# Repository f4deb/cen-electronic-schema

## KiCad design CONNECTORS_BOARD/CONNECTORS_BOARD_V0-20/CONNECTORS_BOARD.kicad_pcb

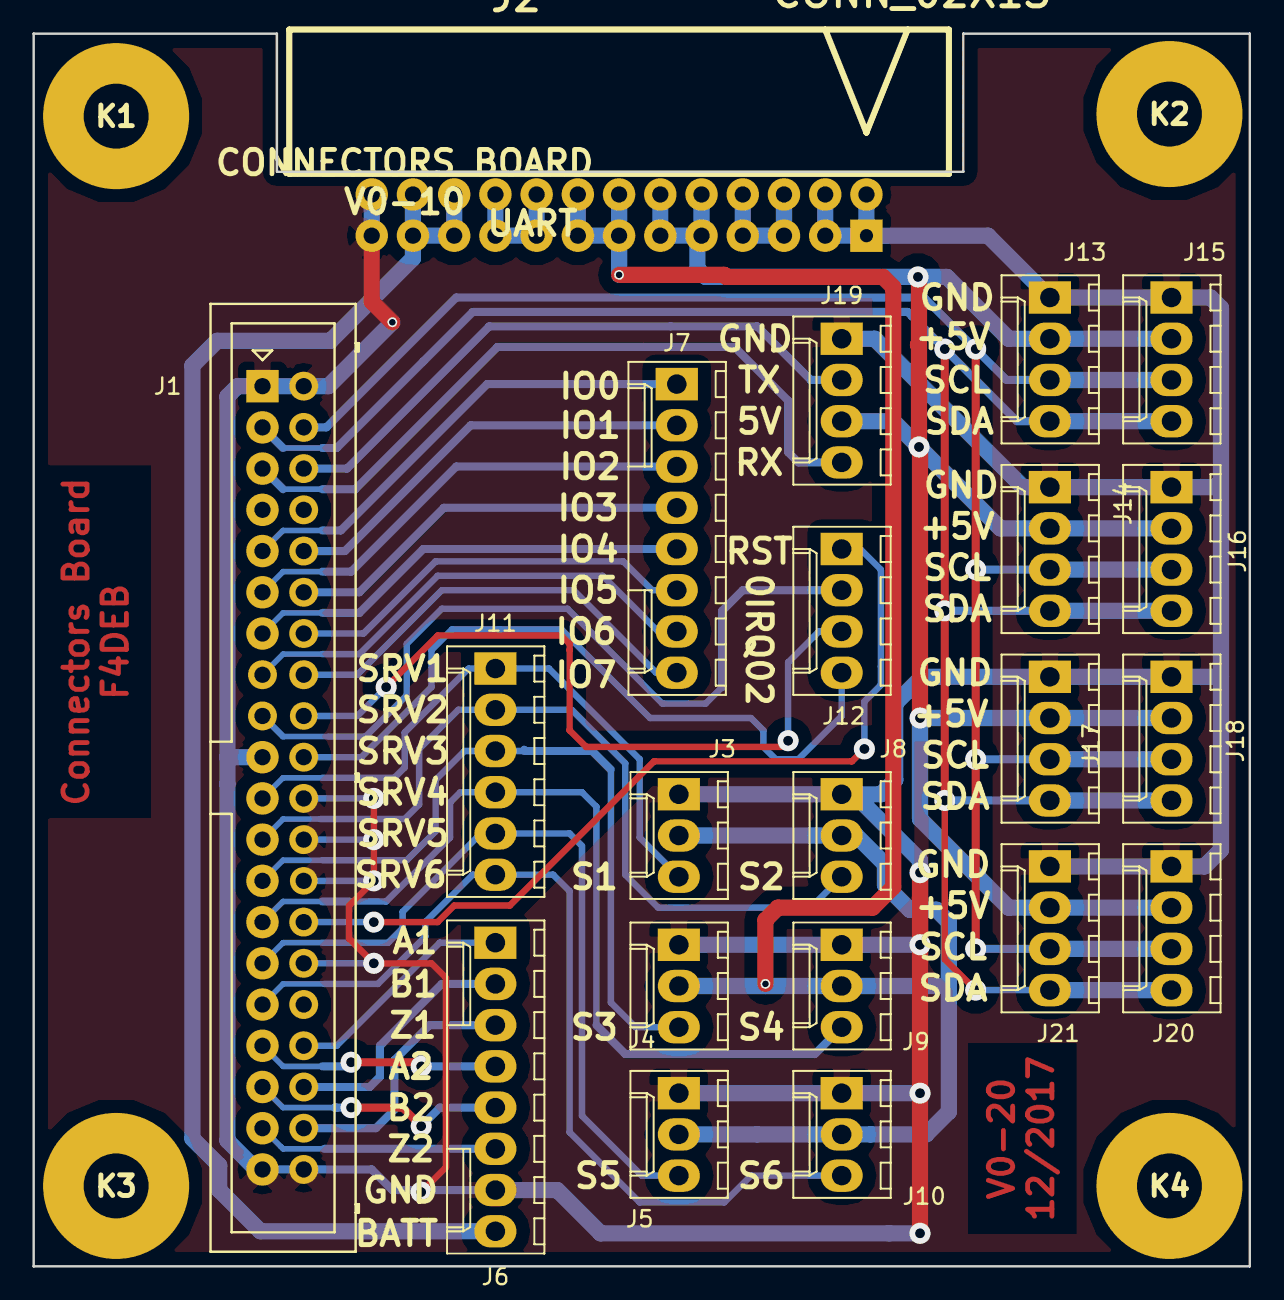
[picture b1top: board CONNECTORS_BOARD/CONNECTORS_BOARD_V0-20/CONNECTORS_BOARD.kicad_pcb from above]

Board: 2 copper layers, 74.9 x 75.9 mm, 25 parts (0 on the bottom side), 34 nets.

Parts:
J1: CONN_02X20; Multicomp_MC9A12-4034_2x20x2.54mm_Straight
J2: CONN_02X13; he10-26c-f
J3, J4, J5, J8, J9, J10: CONN_01X03; Molex_KK-6410-03_03x2.54mm_Straight
J6, J7: CONN_01X08; Molex_KK-6410-08_08x2.54mm_Straight
J11: CONN_01X06; Molex_KK-6410-06_06x2.54mm_Straight
J12, J13, J14, J15, J16, J17, J18, J19, J20, J21: CONN_01X04; Molex_KK-6410-04_04x2.54mm_Straight
K1, K2, K3, K4: COLONETTE

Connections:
+3V3: J2.5, J2.6, J2.7, J2.8
+5V: J2.9, J2.10, J2.11, J2.12, J13.2, J14.2, J15.2, J16.2, J17.2, J18.2, J19.3, J20.2, J21.2
+5VA: J2.13, J2.14, J2.15, J2.16, J3.2, J4.2, J5.2, J8.2, J9.2, J10.2
+12V: J2.17, J2.18, J2.19, J2.20
+BATT: J2.21, J2.22, J2.23, J2.24, J6.8
/A1: J1.34, J6.1
/A2: J1.33, J6.4
/B1: J1.36, J6.2
/B2: J1.35, J6.5
/IO0: J1.9, J7.1
/IO1: J1.10, J7.2
/IO2: J1.11, J7.3
/IO3: J1.12, J7.4
/IO4: J1.13, J7.5
/IO5: J1.14, J7.6
/IO6: J1.15, J7.7
/IO7: J1.16, J7.8
/IRQ0: J1.17, J12.2
/IRQ1: J1.18, J12.3
/IRQ2: J1.20, J12.4
/RST: J1.28, J12.1
/RX: J1.5, J19.4
/SCL: J1.4, J13.3, J14.3, J15.3, J16.3, J17.3, J18.3, J20.3, J21.3
/SDA: J1.3, J13.4, J14.4, J15.4, J16.4, J17.4, J18.4, J20.4, J21.4
/SERV1: J1.21, J3.3, J11.1
/SERV2: J1.23, J8.3, J11.2
/SERV3: J1.25, J4.3, J11.3
/SERV4: J1.27, J9.3, J11.4
/SERV5: J1.29, J5.3, J11.5
/SERV6: J1.31, J10.3, J11.6
/TX: J1.6, J19.2
/Z1: J1.38, J6.3
/Z2: J1.37, J6.6
GND: J1.1, J1.2, J1.19, J1.22, J1.24, J1.26, J1.30, J1.39, J1.40, J2.1, J2.2, J2.3, J2.4, J2.25, J2.26, J3.1, J4.1, J5.1, J6.7, J8.1, J9.1, J10.1, J13.1, J14.1, J15.1, J16.1, J17.1, J18.1, J19.1, J20.1, J21.1

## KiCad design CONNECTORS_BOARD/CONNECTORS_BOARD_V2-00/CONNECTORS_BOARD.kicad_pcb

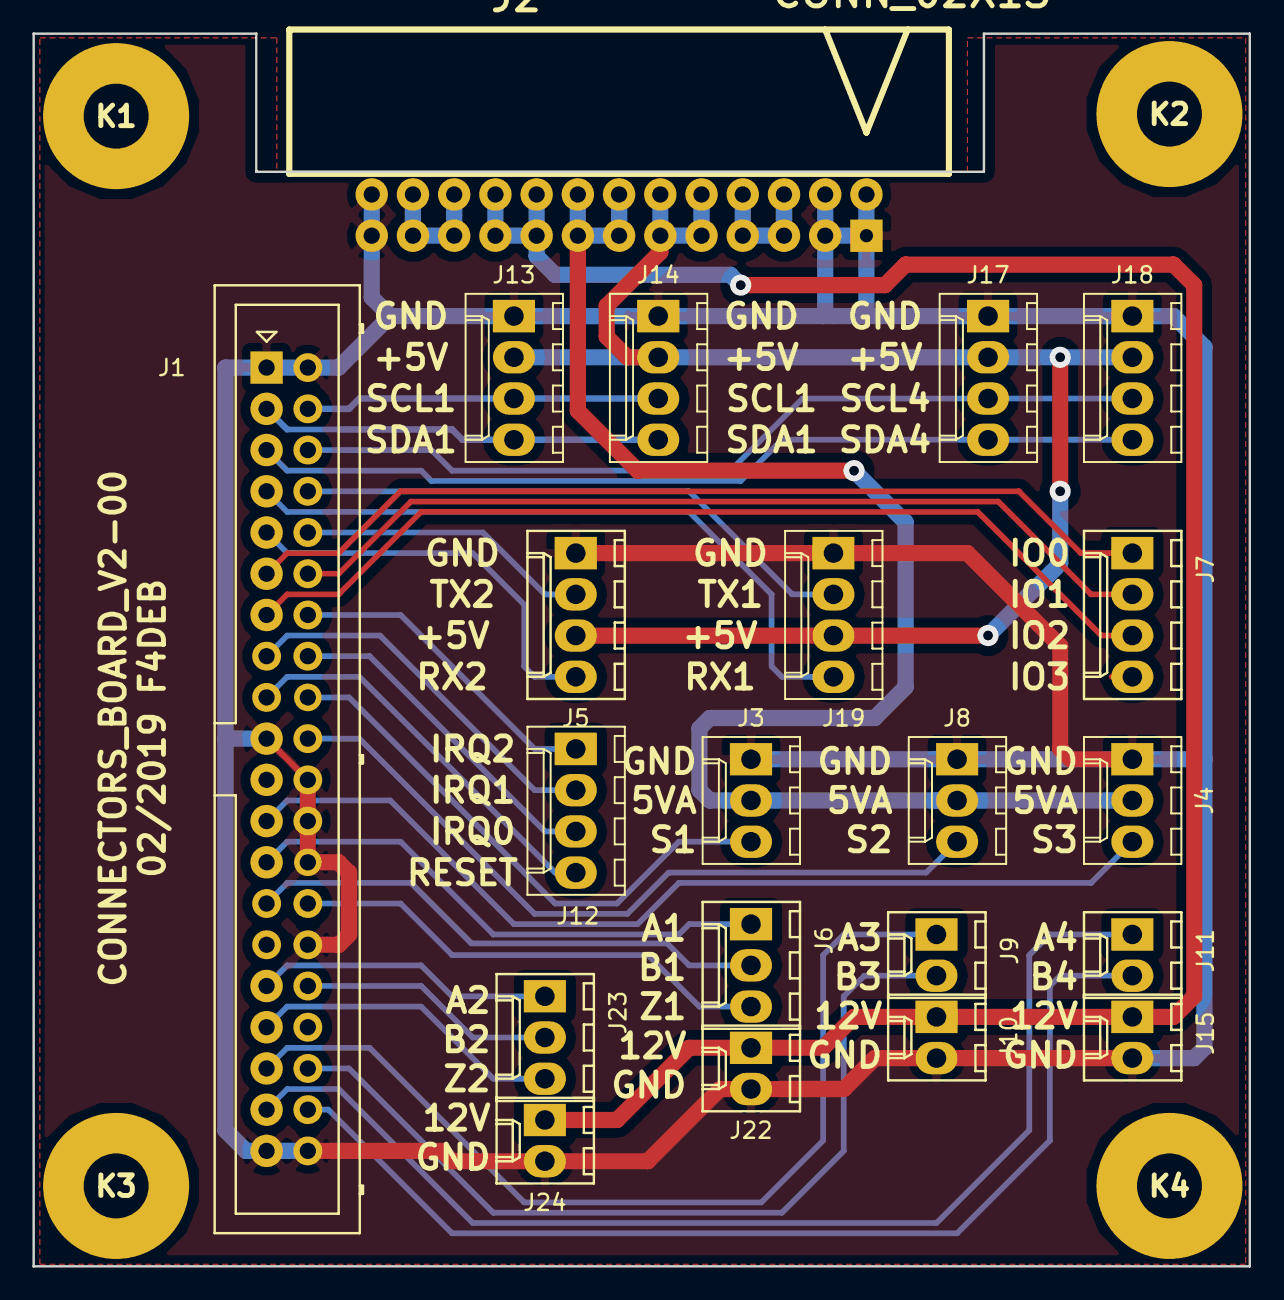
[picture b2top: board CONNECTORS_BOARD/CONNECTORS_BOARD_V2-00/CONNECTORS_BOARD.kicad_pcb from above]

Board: 2 copper layers, 74.9 x 75.9 mm, 25 parts (0 on the bottom side), 34 nets.

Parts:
J1: CONN_02X20; Multicomp_MC9A12-4034_2x20x2.54mm_Straight
J2: CONN_02X13; he10-26c-f
J3, J4, J6, J8, J23: CONN_01X03; Molex_KK-6410-03_03x2.54mm_Straight
J5, J7, J12, J13, J14, J17, J18, J19: CONN_01X04; Molex_KK-6410-04_04x2.54mm_Straight
J9, J10, J11, J15, J22, J24: CONN_01X02; Molex_KK-6410-02_02x2.54mm_Straight
K1, K2, K3, K4: COLONETTE

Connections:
+3V3: J2.5, J2.6, J2.7, J2.8
+5V: J2.9, J2.10, J2.11, J2.12, J5.3, J13.2, J14.2, J17.2, J18.2, J19.3
+5VA: J2.13, J2.14, J2.15, J2.16, J3.2, J4.2, J8.2
+12V: J2.17, J2.18, J2.19, J2.20, J10.1, J15.1, J22.1, J24.1
+BATT: J2.21, J2.22, J2.23, J2.24
/A1: J1.25, J6.1
/A2: J1.31, J23.1
/A3: J1.35, J9.1
/A4: J1.37, J11.1
/B1: J1.27, J6.2
/B2: J1.32, J23.2
/B3: J1.36, J9.2
/B4: J1.38, J11.2
/IO0: J1.11, J7.1
/IO1: J1.12, J7.2
/IO2: J1.13, J7.3
/IRQ0: J1.16, J12.3
/IRQ1: J1.15, J12.2
/IRQ2: J1.14, J12.1
/RST: J1.17, J12.4
/RX1: J1.7, J19.4
/RX2: J1.9, J5.4
/SCL1: J1.4, J13.3, J14.3
/SCL4: J1.6, J17.3, J18.3
/SDA1: J1.3, J13.4, J14.4
/SDA4: J1.5, J17.4, J18.4
/SERV1: J1.18, J3.3
/SERV2: J1.20, J8.3
/SERV3: J1.23, J4.3
/TX1: J1.8, J19.2
/TX2: J1.10, J5.2
/Z1: J1.28, J6.3
/Z2: J1.33, J23.3
GND: J1.1, J1.2, J1.19, J1.22, J1.24, J1.26, J1.30, J1.39, J1.40, J2.1, J2.2, J2.3, J2.4, J2.25, J2.26, J3.1, J4.1, J5.1, J8.1, J10.2, J13.1, J14.1, J15.2, J17.1, J18.1, J19.1, J22.2, J24.2

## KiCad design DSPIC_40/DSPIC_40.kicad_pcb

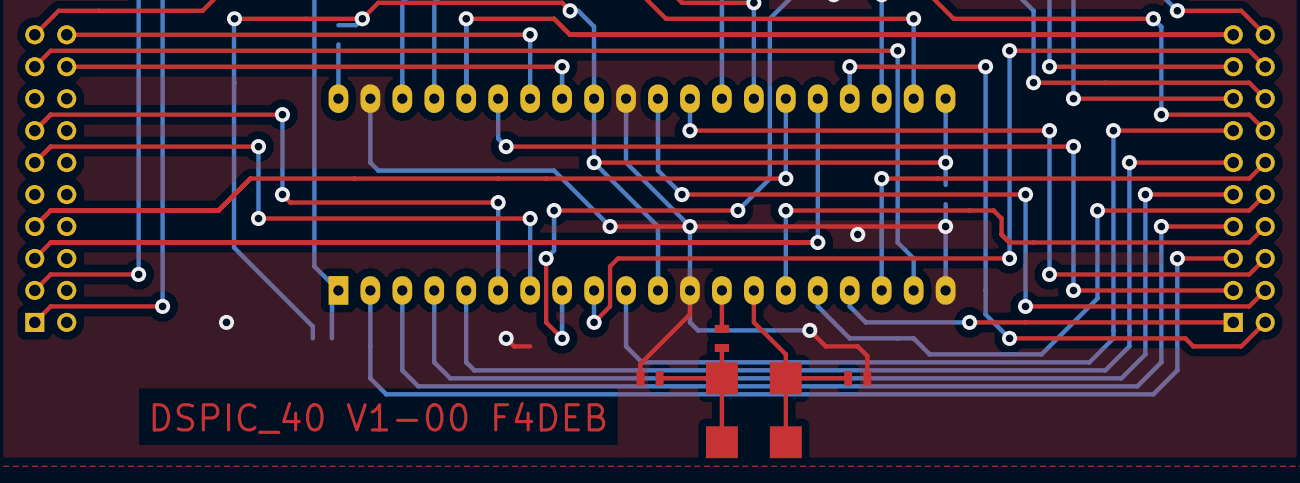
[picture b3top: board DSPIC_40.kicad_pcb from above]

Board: 2 copper layers, 13 parts (0 on the bottom side), 36 nets.

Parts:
C1, C2, C3, C4, C5, C6: C; SM0603_Capa
P1, P2: HE10-20; HE10_20
R1, R2, R3: R; SM0603_Resistor
U1: DSPIC30F4013; DIP-40__600_ELL
X1: CRYSTAL; QTZ

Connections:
+5VD: C3.1, C4.1, C5.1, R1.1, R2.1, U1.11, U1.21, U1.32
/ADC1: P2.11, U1.7
/ADC2: P2.13, U1.6
/D0: P1.5, U1.2
/D1: P1.7, U1.3
/D2: P1.9, U1.4
/D3: P1.11, U1.5
/D4: P1.13, U1.10
/D5: P1.15, U1.38
/D6: P1.17, U1.37
/D7: P1.19, U1.36
/DIR1: P2.17, U1.19
/DIR2: P2.18, U1.33
/IO1: P1.14, U1.23
/IO2: P1.12, U1.18
/OE: P1.3, U1.35
/PGC: P1.16, U1.8
/PGD: P1.18, U1.9
/PWM1: P2.19, U1.22
/PWM2: P2.20, U1.34
/RST: P1.20, R1.2, U1.1
/RSTXY: P1.2, U1.24
/SCL1: P2.5, U1.25
/SDA1: P2.7, U1.26
/SEL1: P1.4, U1.30
/SEL2: P1.6, U1.29
/U1RX: P1.10, U1.16
/U1TX: P1.8, U1.15
/U2RX: P2.1, U1.28
/U2TX: P2.3, U1.27
/XY: P1.1, U1.17
GND: C1.2, C2.2, C3.2, C4.2, C5.2, C6.2, U1.12, U1.20, U1.31, U1.39
unnamed: C6.1, R2.2, U1.40
unnamed: R3.2, U1.13
unnamed: C1.1, R3.1, X1.1
unnamed: C2.1, U1.14, X1.2

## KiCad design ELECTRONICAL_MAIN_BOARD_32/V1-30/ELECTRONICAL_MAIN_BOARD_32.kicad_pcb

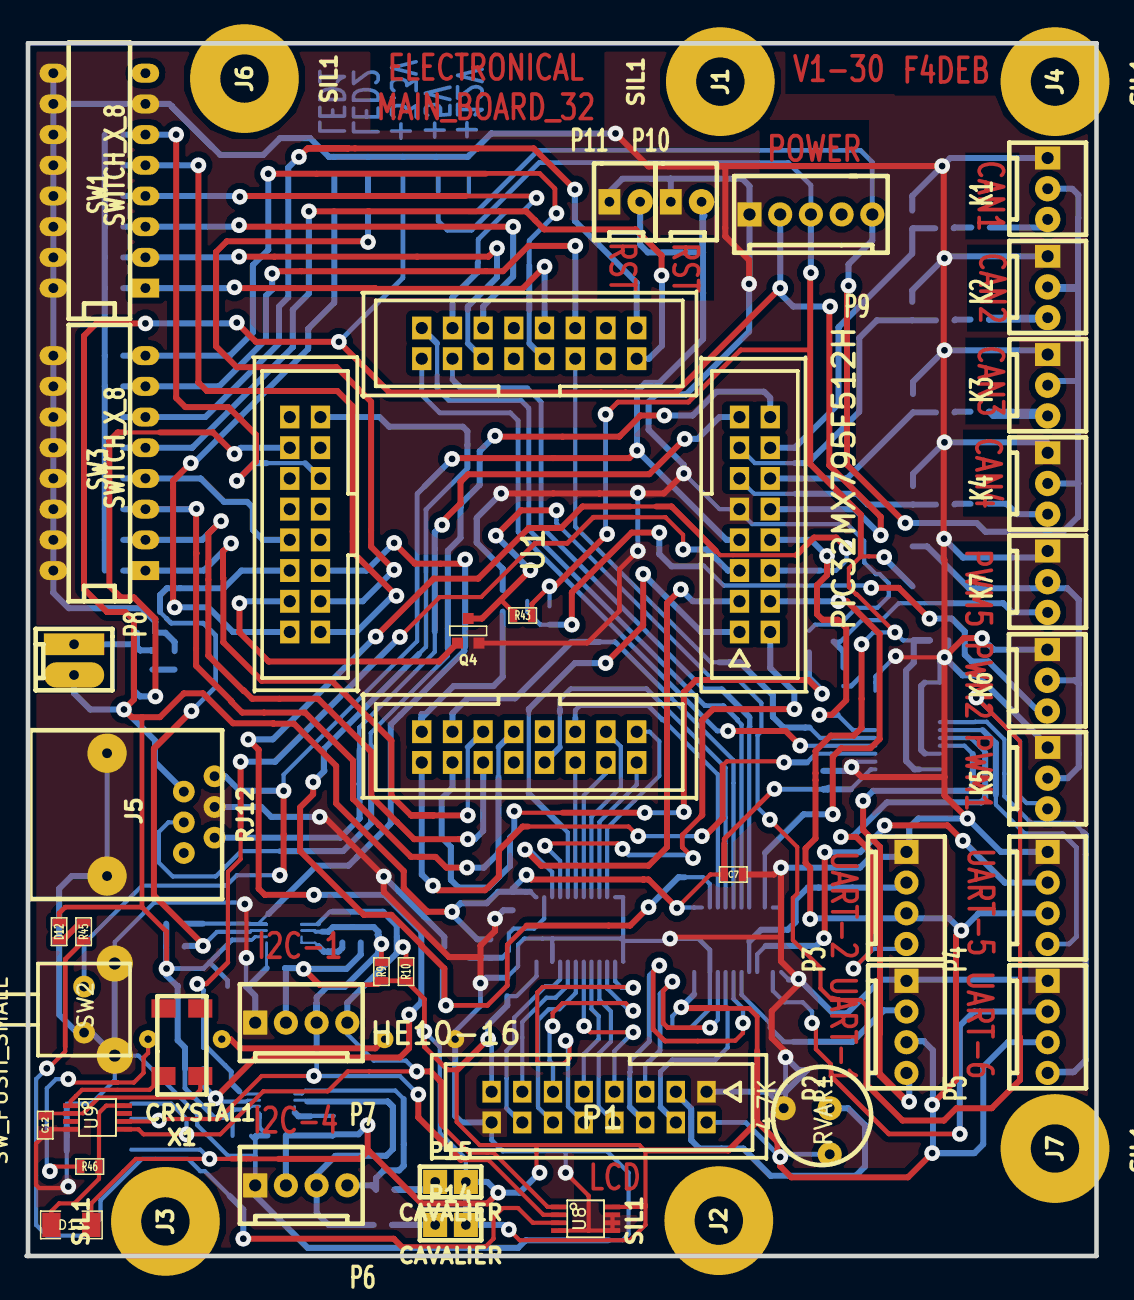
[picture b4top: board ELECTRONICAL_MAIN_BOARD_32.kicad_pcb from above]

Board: 2 copper layers, 88.4 x 100.3 mm, 116 parts (0 on the bottom side), 108 nets.

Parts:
C1, C2, C3, C4, C5, C6, C7, C8, C10, C11: 100n; SM0603_Capa
C9, C13: CP; C-10F
C12: C; SM0603_Capa
D1, D2, D3, D4, D5, D7, D8, D9, D10, D11, D12: LED; SM0603
D13: DIODESCH; SM1206
J1, J2, J3, J4, J6, J7: SIL1; COLONETTE
J5: RJ12; RJ12_E
K1, K2, K3, K4, K5, K6, K7: CONN_3; KK-3
L1: 15uH; SM1206
P1: HE10-16; he10-16d
P2, P3, P4, P5, P6, P7: CONN_4; KK-4
P8, P10, P11: CONN_2; KK-2
P9: CONN_5; KK-5
P14, P15: CAVALIER
Q1, Q2, Q3, Q4: BSS123; SOT23EBC
R1, R9, R10, R13, R14: 1k; SM0603_Resistor
R2, R3, R4, R6: 330; SM0603_Resistor
R5, R16, R17, R18, R19, R20, R21, R22, R23, R24, R25, R26, R27, R28, R29: 10K; SM0603_Resistor
R7, R8, R11, R12: 2.1k; SM0603_Resistor
R30, R31, R32, R33: 3.2k; SM0603_Resistor
R34, R35, R36, R37: 1.5k; SM0603_Resistor
R38: 220k; SM0603
R39: 220k; SM0603_Resistor
R40, R41, R42, R43: 4.7k; SM0603_Resistor
R44: 3..3k; SM0603_Resistor
R45, R46: R; SM0603_Resistor
RVAR1: 4.7K; RV2
SW1, SW3: SWITCH_X_8; DIP-16__300_ELL
SW2: SW_PUSH_SMALL; SW
U1: PIC32MX795F512H; PIC32½64
U2, U3, U6: 74LVCC3245; SSOP24
U4, U5: PCA9306; VSSOP-8
U7: 24C512; SO8E
U8: LM75A; SSOP8
U9: PCF8563; SSOP8
X1: CRYSTAL1; LFXTAL003000

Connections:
+3.3V: C1.1, C2.1, C3.1, C7.1, C8.1, D12.1, J5.2, P8.2, P9.2, R2.1, R7.1, R8.1, R11.1, R12.1, R16.1, R17.1, R18.1, R19.1, R20.1, R21.1, R22.1, R23.1, R24.1, R25.1, R26.1, R27.1, R28.1, R29.1, R42.1, U1.10, U2.1, U2.2, U3.1, U4.2, U5.2, U6.1
+5V: C4.1, C5.1, C6.1, C10.1, C11.1, D13.1, L1.1, P1.2, P1.15, P2.3, P3.3, P4.3, P5.3, P6.2, P7.2, P9.3, P14.2, P15.2, R1.1, R9.1, R10.1, R38.1, R39.1, R40.1, R41.1, R43.1, RVAR1.2, U2.24, U3.24, U6.24, U7.8, U8.8
+12V: K1.2, K2.2, K3.2, K4.2, P9.5, R44.1
/5vto3v3/BE: P1.6, U2.19
/5vto3v3/BRS: P1.4, U2.20
/5vto3v3/BRW: P1.5, U2.21
/5vto3v3/CONTRASTE: P1.3, RVAR1.3
/5vto3v3/D0: U1.60, U6.6
/5vto3v3/D1: U1.61, U6.8
/5vto3v3/D2: U1.62, U6.7
/5vto3v3/D3: U1.63, U6.10
/5vto3v3/D4: U1.64, U6.9
/5vto3v3/D5: U1.1, U6.5
/5vto3v3/D6: U1.2, U6.4
/5vto3v3/D7: U1.3, U6.3
/5vto3v3/E: U1.58, U2.5
/5vto3v3/OC1: Q4.2, U1.46
/5vto3v3/OC1-5V: K5.3, Q4.3, R43.2
/5vto3v3/OC2: Q1.2, U1.49
/5vto3v3/OC2-5V: K6.3, Q1.3, R40.2
/5vto3v3/OC5: Q2.2, U1.52
/5vto3v3/OC5-5V: K7.3, Q2.3, R41.2
/5vto3v3/RS: U1.59, U2.4
/5vto3v3/RW: Q3.2, U1.33, U2.3
/5vto3v3/SCL1: R8.2, U1.44, U4.3
/5vto3v3/SCL1-5V: P7.3, R9.2, U4.6, U7.6, U8.2, U9.6
/5vto3v3/SCL4: R12.2, U1.6, U5.3
/5vto3v3/SCL4-5V: P6.3, R13.2, U5.6
/5vto3v3/SDA1: R7.2, U1.43, U4.4
/5vto3v3/SDA1-5V: P7.4, R10.2, U4.5, U7.5, U8.1, U9.5
/5vto3v3/SDA4: R11.2, U1.5, U5.4
/5vto3v3/SDA4-5V: P6.4, R14.2, U5.5
/5vto3v3/U1RX: U1.50, U3.3
/5vto3v3/U1RX-5V: P2.4, U3.21
/5vto3v3/U1TX: U1.51, U2.6
/5vto3v3/U1TX-5V: P2.2, U2.18
/5vto3v3/U2RX: U1.31, U3.4
/5vto3v3/U2RX-5V: P3.4, U3.20
/5vto3v3/U2TX: U1.32, U2.7
/5vto3v3/U2TX-5V: P3.2, U2.17
/5vto3v3/U5RX: U1.21, U3.5
/5vto3v3/U5RX-5V: P4.4, U3.19
/5vto3v3/U5TX: U1.29, U2.8
/5vto3v3/U5TX-5V: P4.2, U2.16
/5vto3v3/U6RX: U1.8, U3.6
/5vto3v3/U6RX-5V: P5.4, U3.18
/5vto3v3/U6TX: U1.4, U2.10
/5vto3v3/U6TX-5V: P5.2, U2.14
/BD0: P1.7, U6.18
/BD1: P1.8, U6.16
/BD2: P1.9, U6.17
/BD3: P1.10, U6.14
/BD4: P1.11, U6.15
/BD5: P1.12, U6.19
/BD6: P1.13, U6.20
/BD7: P1.14, U6.21
/PIC32/CAN1: D7.1, K1.3
/PIC32/CAN2: D8.1, K2.3
/PIC32/CAN3: D9.1, K3.3
/PIC32/CAN4: D10.1, K4.3
/PIC32/GO: D5.1, P8.1, R5.1, U1.36
/PIC32/LED1: D2.1, R3.2
/PIC32/LED2: D1.1, R4.2
/PIC32/PGEC1: J5.5, U1.15
/PIC32/PGED1: J5.4, U1.16
/PIC32/RST: J5.1, P10.2, P11.2, SW2.2, U1.7
/PIC32/SW0: R26.2, SW3.1, U1.53
/PIC32/SW1: R27.2, SW3.2, U1.54
/PIC32/SW2: R28.2, SW3.3, U1.55
/PIC32/SW3: R29.2, SW3.4, U1.42
/PIC32/SW4: R16.2, SW3.5, U1.17
/PIC32/SW5: R17.2, SW3.6, U1.18
/PIC32/SW6: R18.2, SW3.7, U1.22
/PIC32/SW7: R19.2, SW3.8, U1.23
/PIC32/SW8: R20.2, SW1.1, U1.24
/PIC32/SW9: R21.2, SW1.2, U1.27
/PIC32/SW10: R22.2, SW1.3, U1.28
/PIC32/SW11: R23.2, SW1.4, U1.30
/PIC32/SW12: R24.2, SW1.5, U1.47
/PIC32/SW13: R25.2, SW1.6, U1.37
GND: C1.2, C2.2, C3.2, C4.2, C5.2, C6.2, C7.2, C8.2, C9.2, C10.2, C11.2, C12.2, D1.2, D2.2, D3.2, D4.2, D11.2, J5.3, J5.7, J5.8, K1.1, K2.1, K3.1, K4.1, K5.1, K6.1, K7.1, P1.1, P1.16, P2.1, P3.1, P4.1, P5.1, P6.1, P7.1, P9.1, P10.1, P11.1, Q1.1, Q2.1, Q3.1, Q4.1, R5.2, R6.2, R34.2, R35.2, R36.2, R37.2, RVAR1.1, SW1.7, SW1.9, SW1.10, SW1.11, SW1.12, SW1.13, SW1.14, SW1.15, SW1.16, SW2.1, SW2.3, SW2.4, SW3.9, SW3.10, SW3.11, SW3.12, SW3.13, SW3.14, SW3.15, SW3.16, U1.9, U2.11, U2.12, U2.13, U2.22, U3.2, U3.11, U3.12, U3.13, U3.22, U4.1, U5.1, U6.11, U6.12, U6.13, U6.22, U7.1, U7.2, U7.3, U7.4, U8.4, U8.5, U8.6, U8.7, U9.4
unnamed: D11.1, R44.2
unnamed: K5.2, K6.2, K7.2, L1.2
unnamed: D4.1, R2.2
unnamed: D3.1, R1.2
unnamed: R32.2, R36.1, U1.12
unnamed: R4.1, U1.45
unnamed: R30.2, R34.1, U1.14
unnamed: D5.2, R6.1
unnamed: R3.1, U1.48
unnamed: D8.2, R31.1
unnamed: D10.2, R33.1
unnamed: D7.2, R30.1
unnamed: R31.2, R35.1, U1.13
unnamed: R33.2, R37.1, U1.11
unnamed: D9.2, R32.1
unnamed: R38.2, U4.7, U4.8
unnamed: C9.1, C13.2
unnamed: R45.2, U8.3
unnamed: D12.2, R45.1
unnamed: U9.1, X1.2
unnamed: C13.1, R46.1
unnamed: D13.2, R46.2, U9.8
unnamed: C12.1, U9.2, X1.1
unnamed: P15.1, R14.1
unnamed: R39.2, U5.7, U5.8
unnamed: P14.1, R13.1
unnamed: Q3.3, R42.2, U6.2
